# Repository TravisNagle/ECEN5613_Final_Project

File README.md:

# (WIP) Modular MIDI Control Surface for Reaper

**ECEN 5613 Embedded System Design · Fall 2026 Final Project**
Travis Nagle & Nathan Cohen

An 8051-based MIDI control surface for Reaper. Two motorized faders stay in sync with the DAW, a 16x4 LCD and panel buttons edit presets, and plug-in I2C daughter boards add pots and buttons.

> **Status (2026-10-24):** design phase, nothing built yet. The master board is the **existing class dev board**, and every new circuit is **hand-built on perf boards** (no custom PCB). The authoritative hardware spec is [Hardware_Map.md](Hardware_Map.md) **Rev 13**; open decisions are in its section 9. The PDR (10/19) described a foot controller with one fader. The changes since then are in Hardware_Map Appendix B.

## Documents

| File | What it is |
|---|---|
| [Hardware_Map.md](Hardware_Map.md) | **Authoritative hardware spec (Rev 13)**: architecture, class-board changes, pin map, memory map, netlist (Appendix A), build stages, open items |
| [hardware/kicad/ESD_Final/ESD_Final_schematic.pdf](hardware/kicad/ESD_Final/ESD_Final_schematic.pdf) | **Schematic** (KiCad 10, one sheet per board), generated from [hardware/kicad/tools/design.py](hardware/kicad/tools/design.py) |
| [hardware/panel/](hardware/panel/) | Laser-cut acrylic top panel (SVG generator) |
| [hardware/Perfboard_Order_Notes.md](hardware/Perfboard_Order_Notes.md) | Kit parts mapping, on-hand modules, Digi-Key order (not yet placed) and alternates |
| [docs/f26finalproject_8-24-2026.pdf](docs/f26finalproject_8-24-2026.pdf) | Course final-project specification (deliverables, report and submission rules) |
| [docs/F26_PDR_TravisNagle_NathanCohen.pptx](docs/F26_PDR_TravisNagle_NathanCohen.pptx) | Preliminary design review slides (10/19) |
| [docs/MIDI-Controller.pdf](docs/MIDI-Controller.pdf) | PDR-era design document (single fader) |
| [docs/archive/](docs/archive/) | Superseded documents (Rev 10 review of the dropped PCB design) |
| [reference/](reference/) | Read-only: class dev board KiCad project, BOM, Lab 3 SPLD and memory map; fader datasheet; parts-kit list |
| [AGENTS.md](AGENTS.md) | Rules and conventions for AI agents working in this repo |

The custom-PCB draft (`kicad/ESD_Main`, Rev 12) was removed on 2026-10-24. It is still in the git history at commit `735803c`.

---

## Features

- **Two motorized faders, synced both ways:** moving a fader changes Reaper's track volume, and Reaper's automation moves the fader. A capacitive touch sensor on each fader knob tells the firmware when a hand is on it, so the motor never fights the user.
- **USB-MIDI with no drivers:** the 8051 UART talks to a KB2040 acting as a class-compliant USB-MIDI device; Reaper uses its built-in Mackie Control Universal support.
- **LCD and panel buttons:** 16x4 character LCD on the memory-mapped bus, a five-way D-pad and one button per fader for menus and presets.
- **Presets:** stored in a 24C16 I2C EEPROM.
- **Expression pedal:** TRS input on the fader ADC, sent as a MIDI CC.
- **Daughter boards:** pot and button boards on an I2C bus over RJ45 cables, in any order; the master finds them by address scan.

---

## System Overview

```
                 +---------------- class dev board (master) ----------------+
 9 V adapter --> | AT89C51RC2 @ 11.0592 MHz, '373 latch, ATF16V8B decode,   |
                 | MAX232 + DB9 (FLIP / PC), 7805                           |
                 +---+-----------------+----------------+-------------+-----+
                     | AD bus + decode | PCA PWM, SPI   | UART        | I2C
                     v                 v                v             v
              LCD 16x4,          TB6612 -> 2 faders  KB2040 USB-MIDI  24C16 presets,
              '273 dir latch,    MCP3008 ADC         (level shifter)  RJ45 bus -> pot / button
              '244 buttons       (faders, pedal)         |                daughter boards
                                                         v
                                                PC: Reaper (Mackie Control)
```

Full block diagram, pin map and memory map: [Hardware_Map.md](Hardware_Map.md) sections 1-3.

| XRAM address | Device |
|---|---|
| 0x0000-0x03FF | On-chip XRAM |
| 0xF000 | Motor direction latch (write) |
| 0xF400-0xF403 | LCD (command / data / busy / data read) |
| 0xF800 | Button buffer (read) |
| 0xFFFF | Virtual debug port (logic-analyzer trigger) |

---

## Firmware Architecture

Interrupts only move bytes and set flags; all real work runs in a cooperative main loop.

| Interrupt / hardware | Job |
|---|---|
| UART (Timer 2) | Link to the KB2040: RX into a ring buffer, TX from a ring buffer. 31,250 baud MIDI or 115,200 baud packets (Hardware_Map `OPEN` #4) |
| Timer 0, mode 2 (high priority) | Soft-UART debug TX at 9,600 baud on P1.0 |
| Timer 1, mode 1 | 1 ms system tick |
| PCA | 8-bit hardware PWM at 10.8 kHz for two motors (no CPU cost) |

| Main-loop module | Job |
|---|---|
| MIDI parser | Status/data state machine, running status, real-time bytes (Reaper feedback only) |
| Button scan | Read 0xF800 at about 100 Hz, 20 ms debounce, short and long press |
| Fader control | MCP3008 reads, PD loop at 250-500 Hz, deadband brake, stall timeout, staggered starts |
| MCU link | 14-bit pitch bend both ways; touch notes from the knob touch sensors (0xF800 bit 7, P1.5) |
| Pedal | Averaging, calibration, hysteresis -> CC 11 |
| LCD + UI | Shadow copy, menu, transient messages |
| Presets | 24C16 records with checksum |
| I2C daughters | Address scan, PCF8574 buttons/LEDs, pot ADC reads, bus recovery |

The PDR's CPU budget (single fader, 1 kHz loop, MIDI merge) no longer applies. Re-measure the budget on hardware.

---

## Mackie Control Messages Used

| Message | Meaning |
|---|---|
| `E0 ll mm` / `E1 ll mm` | Fader 1 / 2 position (14-bit, both directions) |
| `90 68 7F` / `90 68 00` | Fader 1 touch / release (fader 2: note `69`) |
| `90 18+n`, `10+n`, `08+n`, `00+n` | Select / Mute / Solo / Rec for strip n |
| `90 5F 7F` / `90 5E 7F` / `90 5D 7F` | Record / Play / Stop |
| `B0 0B vv` | Expression pedal (CC 11) |

Starting point only; the full mapping is in Hardware_Map section 5.

---

## Setup

### Hardware
1. Power everything from one **9 V, 2 A or more** adapter in the class board jack; it feeds the logic and the fader motors (Hardware_Map section 3.9).
2. Plug the KB2040 into the PC by USB-C. It shows up as a USB-MIDI device.
3. Set `JP_RX` to **KB** for normal use, or **PC** for FLIP and the DB9 terminal.

### Reaper
1. **Options → Preferences → Audio → MIDI Devices:** confirm the KB2040 appears; enable its input and output.
2. **Preferences → Control/OSC/Web → Add → Mackie Control Universal:** set the MIDI input and output to the KB2040.
3. Optional: assign the pedal to any plugin parameter with **Param → Learn** in the FX window.

### Fallback (if the USB-MIDI bridge fails)
MIDI bytes go out the class board DB9 at 115,200 baud → USB-RS232 adapter → [Hairless MIDI](https://projectgus.github.io/hairless-midiserial/) → [loopMIDI](https://www.tobias-erichsen.de/software/loopmidi.html) → Reaper.

---

## Building and Flashing

> Firmware is not written yet; these steps will be finalized with the first build.

```bash
cd firmware
sdcc -mmcs51 --model-large main.c
packihx main.ihx > main.hex
```

Flash `main.hex` with Atmel FLIP over the class board DB9 (`JP_RX` in the **PC** position; hold the PSEN button through reset to enter the bootloader). The KB2040 runs a CircuitPython bridge script (to be added under `firmware/`).

---

## Milestones

Rebased from the PDR milestones for the Rev 13 scope; the team still needs to confirm owners and dates.

| | Milestone | Owner | Target | Phase |
|---|---|---|---|---|
| M1 | MIDI link: Timer 2 UART, KB2040 bridge, Reaper receives notes | Both | 11/1 | P1 |
| M2 | Debug port, panel buttons via the '244 | Travis | 11/8 | P1 |
| M3 | MCP3008: fader positions and pedal as CC | Nathan | 11/8 | P1 |
| M4 | MIDI from Reaper: parser, MCU feedback | Travis | 11/22 | P1 |
| M5 | LCD, presets (24C16), menu | Travis | 11/29 | P1-P2 |
| M6 | Motorized faders: TB6612, PD loop, MCU link (2 faders) | Nathan | 11/29 | P1-P2 |
| M7 | I2C daughter boards (pot, button) over RJ45 | Both | 11/29 | P3 |
| M8 | Stretch: MIDI clock tempo sync | Both | If ahead | |

Feature freeze **11/30** · Demo **12/4** · Return kit items (including the NVSRAM) **12/7** · Report **12/9**

---

## Repository Layout

```
Hardware_Map.md   hardware spec (start here)
hardware/         kicad/ (schematic project, libraries, generators), panel/ (acrylic panel), parts and order notes
spld/             (planned) final.pld, its simulation input and .jed
firmware/         8051 C source (SDCC) and the KB2040 bridge script
tools/            test scripts (MIDI-OX configs, benchmarks)
docs/             course spec, PDR deck, design doc; archive/ for superseded documents
reference/        class dev board, fader datasheet, parts kit; read-only: copy, do not edit
```

---

## References

- Atmel AT89C51RB2/RC2 Datasheet (doc4180), Errata (doc4181), 8051 Hardware Manual (doc4316)
- [MIDI 1.0 Electrical Specification (CA-033)](https://midi.org/wp-content/uploads/wpforo/default_attachments/1709416667-ca33-MIDI-10-Electrical-Specification-Update.pdf)
- [Summary of MIDI 1.0 Messages](https://midi.org/summary-of-midi-1-0-messages)
- [REAPER Mackie Control source (`csurf_mcu.cpp`)](https://github.com/justinfrankel/reaper-sdk/blob/main/reaper-plugins/reaper_csurf/csurf_mcu.cpp)
- [Microchip MCP3008](https://ww1.microchip.com/downloads/en/DeviceDoc/21295d.pdf), Toshiba TB6612FNG, TI [SN74AHC157](https://www.ti.com/lit/ds/symlink/sn74ahc157.pdf), [SN74HCT244](https://www.ti.com/lit/ds/symlink/sn74hct244.pdf), [CD74HCT273](https://www.ti.com/lit/ds/symlink/cd74hct273.pdf), [MAX232](https://www.ti.com/lit/ds/symlink/max232.pdf), NXP PCF8574
- [Adafruit KB2040](https://learn.adafruit.com/adafruit-kb2040), CircuitPython `usb_midi`
- Terwin SM100 motor fader: [reference/motor_slider_datasheet.pdf](reference/motor_slider_datasheet.pdf)

## AI use

Parts of the hardware documents were drafted with AI assistance (Anthropic Claude) and reviewed by the team. The course requires AI use to be fully documented in the final report, and AI may not be used to write report text.

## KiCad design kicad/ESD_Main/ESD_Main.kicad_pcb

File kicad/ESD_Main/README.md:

# ESD_Main: main board (KiCad 10)

**Status (2026-10-20, 02:10): first complete draft, DO NOT ORDER YET.** Schematic: ERC 0 violations, netlist matches the design data (178 parts, 555 pins). PCB: 100 % routed by Freerouting, DRC 0 errors / 0 unconnected / 0 schematic-parity issues; the only warnings are 14 `silk_edge_clearance` on the edge connectors (silk at the board edge by design). It has not been reviewed by a person in KiCad yet; work through the checklist below first.

Spec: [Hardware_Map.md](../../Hardware_Map.md) Rev 12 (pin map section 3.2, netlist Appendix A, open items section 9). Schematic PDF: [ESD_Main_schematic.pdf](ESD_Main_schematic.pdf). Renders: [top](fab/ESD_Main_top.png), [bottom](fab/ESD_Main_bottom.png). Fab files: [fab/](fab/) (Gerbers + drill zip for JLCPCB, BOM CSV).

## What is on the board

- 200 x 150 mm, 2 layers, 1.6 mm, GND pour both sides. The PCB is the **front panel**: faders, LCD, D-pad and buttons on top.
- **Three Terwin SM100 motor faders** (footprint from [the datasheet](../../reference/motor_slider_datasheet.pdf)) along the 150 mm depth; each motor hangs through a **26 x 3.2 mm notch** in the back edge. Motor wires go to 2-pin headers MOTOR 1-3 (J10-J12). H-bridges U12/U13 sit between the faders; fader buttons SW8-SW10 beside each fader's front end (no room below them).
- **LCD** (Lab 4 kit: Samsung 16x4, 14-pin single row, no backlight) on 15 mm+ M2.5 standoffs and a tall header **over the bus logic** (8051, '373, SPLD, '273, '244, '14, EEPROM). The LCD lifts off for debugging; the test points are outside its outline.
- Back edge: 12 V barrel (J1), MIDI IN/OUT DIN-5 (J5/J6), pedal TRS (J13). Left edge: PC DB9 (J7). Front: D-pad, RESET, BOOT (PSEN), contrast trimmer, power/status LEDs, TTL PC (J8) and TTL DEBUG (J9) FTDI-style headers, daughter-bus IDC (J14), test points.
- Reference designators differ from the spec's (for example spec U7 SPLD = board U4, spec J10 LCD = board J4); each part's `Note` field in the schematic gives the spec name.

## Check before ordering (needs a person)

1. **Fader footprint**: print the top copper/silk at 1:1 (or use KiCad's 3D/measure) and lay a real fader on it: pins 1/2 and 3/T, the two locating bosses (Ø2.1 NPTH at ±48 mm) and the motor notch.
2. **LCD**: confirm with a ruler: outline 87 x 60, holes 82 x 55 apart, pin 1 at 10.0 mm from the left edge and 2.5 mm from the top. Count 16 vs 20 characters at first power-up (firmware constant).
3. **DIN-5 (Same Sky SDS-50J)** and **barrel jack** orientation: mating faces flush with the back edge (check the 3D view).
4. **Standoffs**: board standoffs >= 16 mm (motor + terminals stick out about 14.5 mm below the top surface); LCD standoffs high enough to clear the socketed DIPs underneath.
5. Run DRC in KiCad, view all copper layers, and look at the motor/12 V traces (1.0/1.2 mm) and the long ADC SPI traces that run under the faders.
6. JLCPCB: upload `fab/ESD_Main_gerbers.zip`; 2 layers, 1.6 mm, HASL lead-free, order a stencil for the 0805 parts.
7. BOM: `fab/ESD_Main_BOM.csv` has MPNs; supplier, URL and cost columns are still blank (course BOM needs them).

## How it was made (and how to change it)

The schematic and the initial board were **generated by scripts** from two data files, then auto-routed with Freerouting 1.9.0:

| File | Role |
|---|---|
| [kicad/tools/esd_main_design.py](../tools/esd_main_design.py) | every part: symbol, footprint, phase, MPN, pin -> net |
| [kicad/tools/esd_main_placement.py](../tools/esd_main_placement.py) | board outline, notches, fixed positions, placement zones |
| [kicad/tools/gen_esd_main.py](../tools/gen_esd_main.py) | writes the schematic (ERC + netlist checked) |
| [kicad/tools/gen_esd_main_pcb.py](../tools/gen_esd_main_pcb.py) | builds, routes (Freerouting) and exports the board |
| [kicad/tools/check_esd_main.py](../tools/check_esd_main.py) | netlist export vs design data cross-check |

```bash
python3 kicad/tools/gen_esd_main.py
KPY=/Applications/KiCad/KiCad.app/Contents/Frameworks/Python.framework/Versions/Current/bin/python3
$KPY kicad/tools/gen_esd_main_pcb.py --stage all --jar /path/to/freerouting-1.9.0.jar --work /tmp/esd_route
```

`--jar` and `--work` default to a path on Nathan's machine, so pass your own. Freerouting needs Java 17+ and is random: each run takes 2-5 minutes and results vary.

**Important**: regenerating overwrites the schematic and board. Once anyone hand-edits in KiCad (routing clean-up, moving parts), stop regenerating the board and make further changes in KiCad (keep the design data file in step for the schematic, or edit the schematic in KiCad too and say so here).

AI use: the schematic/PCB generators and this draft were produced with AI assistance (Anthropic Claude) and must be reviewed by the team; record this in the final report.

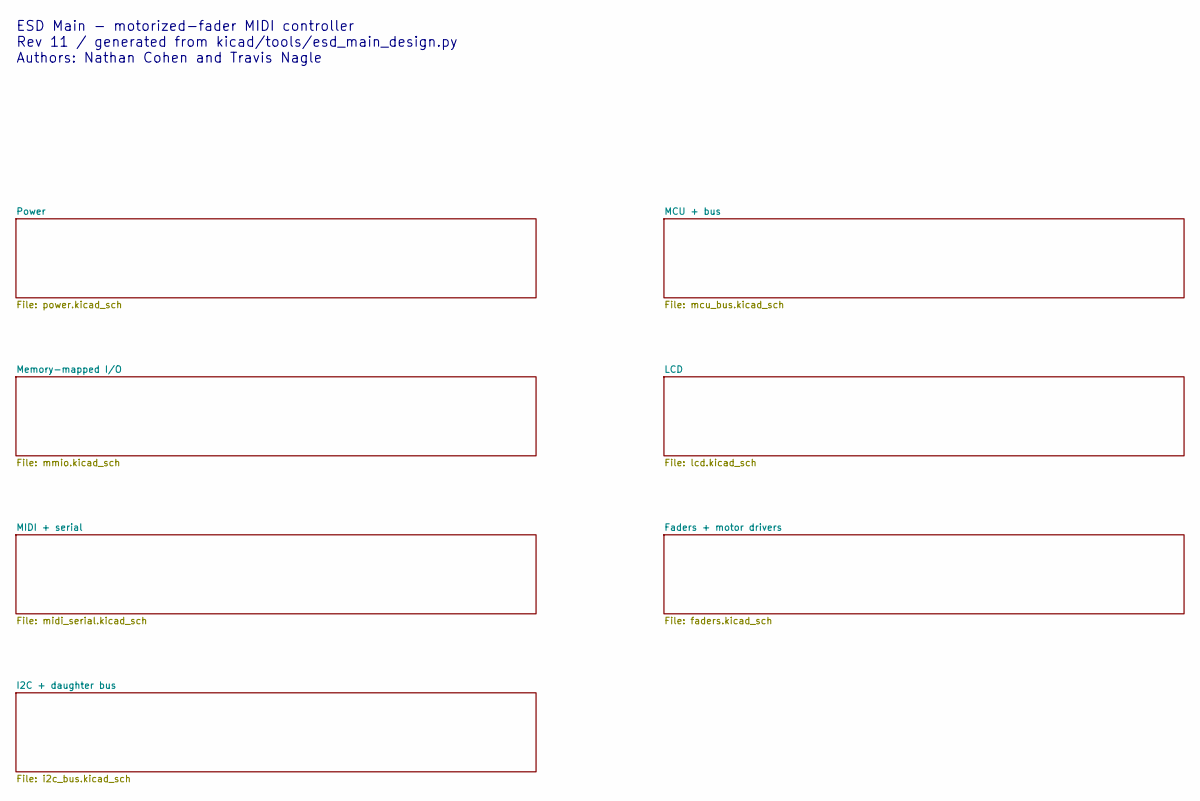
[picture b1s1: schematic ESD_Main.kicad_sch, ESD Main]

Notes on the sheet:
ESD Main - motorized-fader MIDI controller Rev 11 / generated from kicad/tools/esd_main_design.py Authors: Nathan Cohen and Travis Nagle

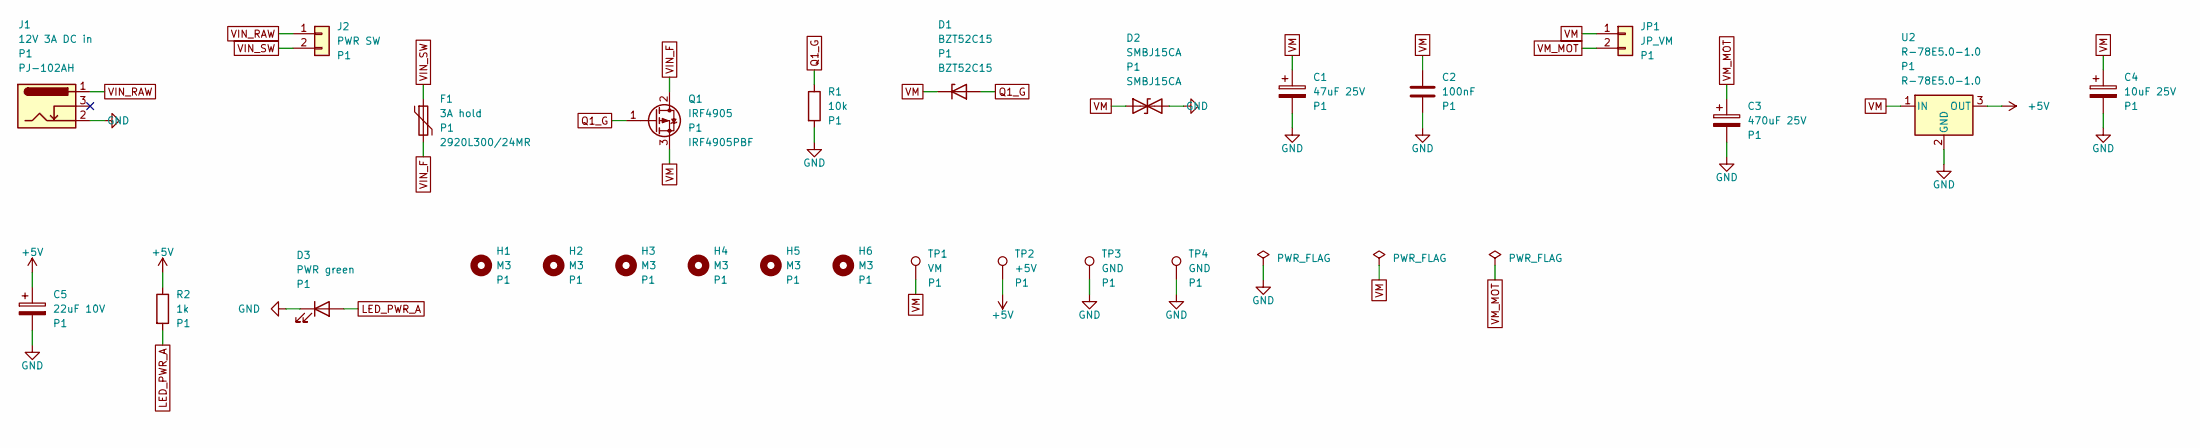
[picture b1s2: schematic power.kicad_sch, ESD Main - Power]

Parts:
C1: 47uF 25V; CP_Radial_D6.3mm_P2.50mm
C2: 100nF; C_0805_2012Metric
C3: 470uF 25V; CP_Radial_D10.0mm_P5.00mm
C4: 10uF 25V; CP_Radial_D5.0mm_P2.00mm
C5: 22uF 10V; CP_Radial_D5.0mm_P2.00mm
D1: BZT52C15; D_SOD-123; MPN BZT52C15
D2: SMBJ15CA; D_SMB; MPN SMBJ15CA
D3: PWR green; LED_0805_2012Metric
F1: 3A hold; Fuse_2920_7451Metric; MPN 2920L300/24MR
H1, H2, H3, H4, H5, H6: M3; MountingHole_3.2mm_M3
J1: 12V 3A DC in; BarrelJack_CUI_PJ-102AH_Horizontal; MPN PJ-102AH
J2: PWR SW; PinHeader_1x02_P2.54mm_Vertical
JP1: JP_VM; PinHeader_1x02_P2.54mm_Vertical
Q1: IRF4905; TO-220-3_Vertical; MPN IRF4905PBF
R1: 10k; R_0805_2012Metric
R2: 1k; R_0805_2012Metric
TP1: VM; TestPoint_THTPad_D1.5mm_Drill0.7mm
TP2: +5V; TestPoint_THTPad_D1.5mm_Drill0.7mm
TP3, TP4: GND; TestPoint_THTPad_D1.5mm_Drill0.7mm
U2: R-78E5.0-1.0; TO-220-3_Vertical; MPN R-78E5.0-1.0

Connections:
+5V: C5.1, R2.1, TP2.1, U2.3 (OUT); also elsewhere on the board
GND: C1.2, C2.2, C3.2, C4.2, C5.2, D2.2 (A2), D3.1 (K), J1.2, R1.2, TP3.1, TP4.1, U2.2 (GND); also elsewhere on the board
LED_PWR_A: D3.2 (A), R2.2
Q1_G: D1.2 (A), Q1.1 (G), R1.1
VIN_F: F1.2, Q1.2 (D)
VIN_RAW: J1.1, J2.1
VIN_SW: F1.1, J2.2
VM: C1.1, C2.1, C4.1, D1.1 (K), D2.1 (A1), JP1.1, Q1.3 (S), TP1.1, U2.1 (IN)
VM_MOT: C3.1, JP1.2; also elsewhere on the board

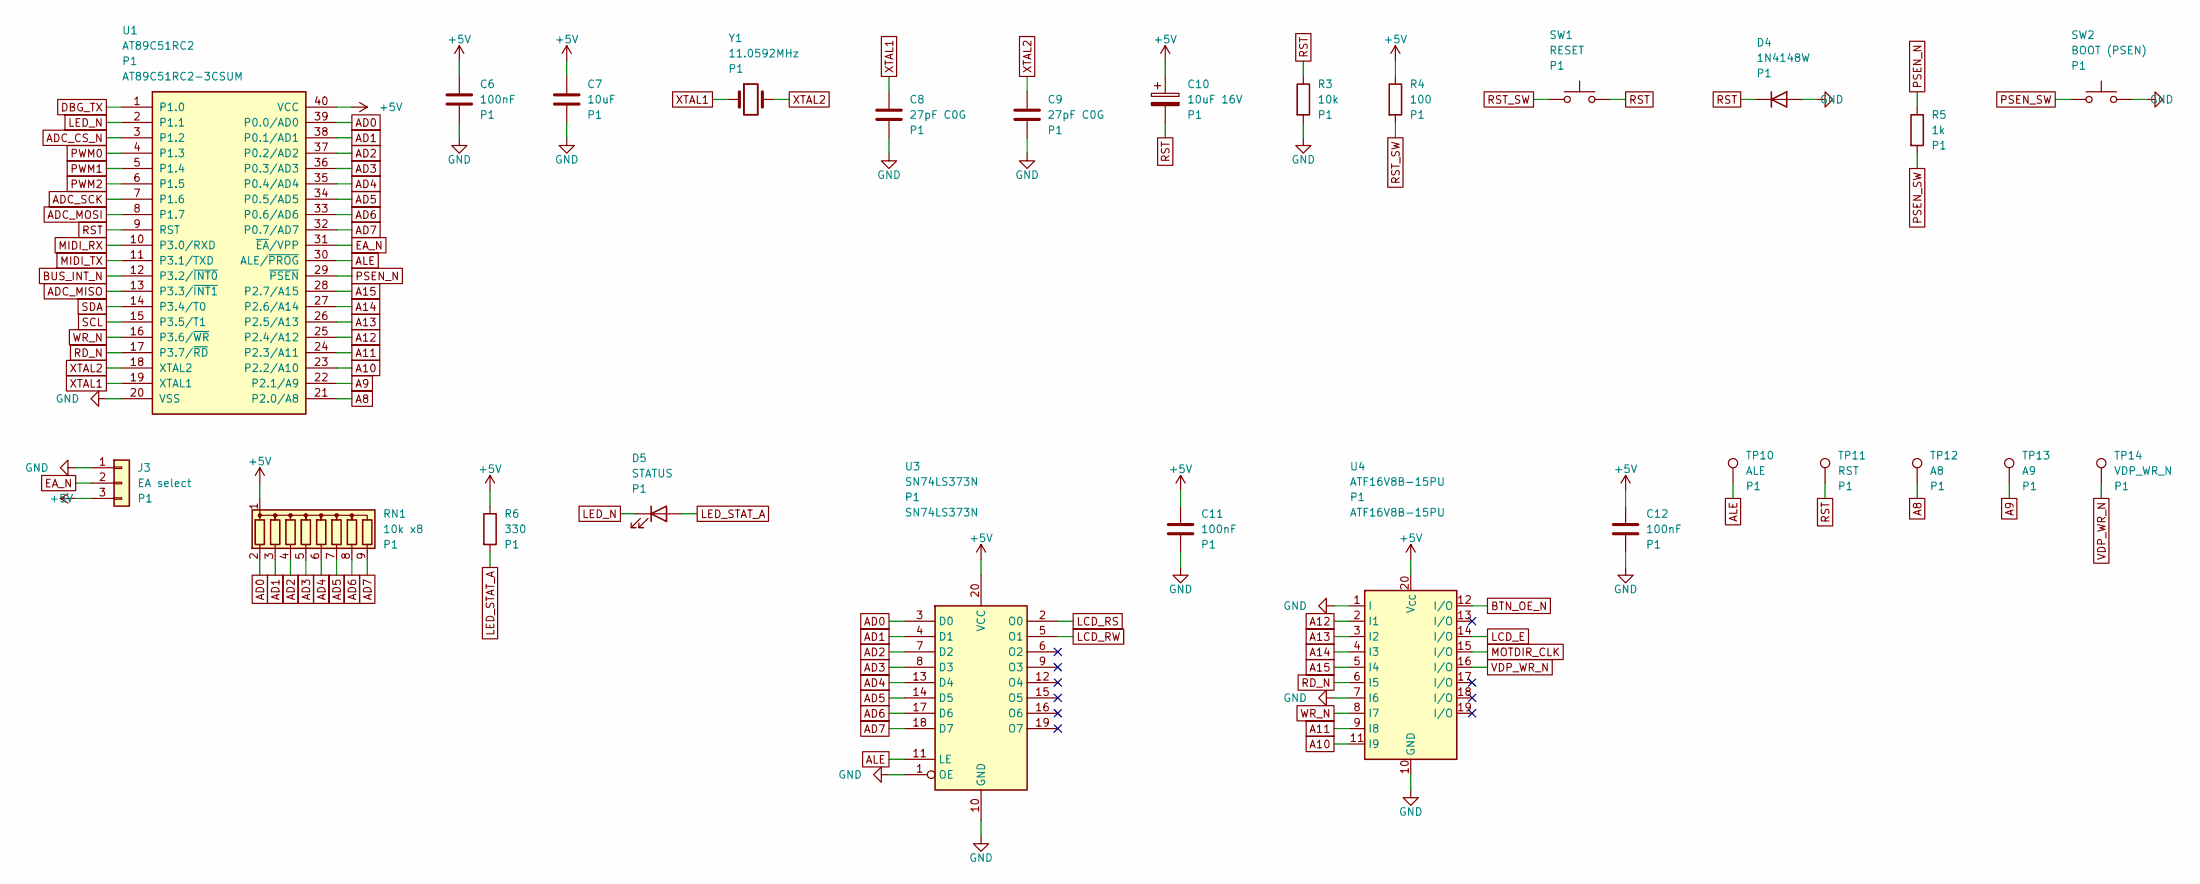
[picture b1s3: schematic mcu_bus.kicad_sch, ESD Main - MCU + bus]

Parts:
C6, C11, C12: 100nF; C_0805_2012Metric
C7: 10uF; C_0805_2012Metric
C8, C9: 27pF C0G; C_0805_2012Metric
C10: 10uF 16V; CP_Radial_D5.0mm_P2.00mm
D4: 1N4148W; D_SOD-123
D5: STATUS; LED_0805_2012Metric
J3: EA select; PinHeader_1x03_P2.54mm_Vertical
R3: 10k; R_0805_2012Metric
R4: 100; R_0805_2012Metric
R5: 1k; R_0805_2012Metric
R6: 330; R_0805_2012Metric
RN1: 10k x8; R_Array_SIP9
SW1: RESET; SW_PUSH_6mm
SW2: BOOT (PSEN); SW_PUSH_6mm
TP10: ALE; TestPoint_THTPad_D1.5mm_Drill0.7mm
TP11: RST; TestPoint_THTPad_D1.5mm_Drill0.7mm
TP12: A8; TestPoint_THTPad_D1.5mm_Drill0.7mm
TP13: A9; TestPoint_THTPad_D1.5mm_Drill0.7mm
TP14: VDP_WR_N; TestPoint_THTPad_D1.5mm_Drill0.7mm
U1: AT89C51RC2; DIP-40_W15.24mm_Socket; MPN AT89C51RC2-3CSUM
U3: SN74LS373N; DIP-20_W7.62mm_Socket; MPN SN74LS373N
U4: ATF16V8B-15PU; DIP-20_W7.62mm_Socket; MPN ATF16V8B-15PU
Y1: 11.0592MHz; Crystal_HC49-U_Vertical

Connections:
+5V: C6.1, C7.1, C10.1, C11.1, C12.1, J3.3, R4.1, R6.1, RN1.1 (common), U1.40 (VCC), U3.20 (VCC), U4.20 (V_{CC}); also elsewhere on the board
A8: TP12.1, U1.21 (P2.0/A8)
A9: TP13.1, U1.22 (P2.1/A9)
A10: U1.23 (P2.2/A10), U4.11 (I9)
A11: U1.24 (P2.3/A11), U4.9 (I8)
A12: U1.25 (P2.4/A12), U4.2 (I1)
A13: U1.26 (P2.5/A13), U4.3 (I2)
A14: U1.27 (P2.6/A14), U4.4 (I3)
A15: U1.28 (P2.7/A15), U4.5 (I4)
AD0: RN1.2 (R1), U1.39 (P0.0/AD0), U3.3 (D0); also elsewhere on the board
AD1: RN1.3 (R2), U1.38 (P0.1/AD1), U3.4 (D1); also elsewhere on the board
AD2: RN1.4 (R3), U1.37 (P0.2/AD2), U3.7 (D2); also elsewhere on the board
AD3: RN1.5 (R4), U1.36 (P0.3/AD3), U3.8 (D3); also elsewhere on the board
AD4: RN1.6 (R5), U1.35 (P0.4/AD4), U3.13 (D4); also elsewhere on the board
AD5: RN1.7 (R6), U1.34 (P0.5/AD5), U3.14 (D5); also elsewhere on the board
AD6: RN1.8 (R7), U1.33 (P0.6/AD6), U3.17 (D6); also elsewhere on the board
AD7: RN1.9 (R8), U1.32 (P0.7/AD7), U3.18 (D7); also elsewhere on the board
ADC_CS_N: U1.3 (P1.2); also elsewhere on the board
ADC_MISO: U1.13 (P3.3/~INT1); also elsewhere on the board
ADC_MOSI: U1.8 (P1.7); also elsewhere on the board
ADC_SCK: U1.7 (P1.6); also elsewhere on the board
ALE: TP10.1, U1.30 (ALE/~PROG), U3.11 (LE)
BTN_OE_N: U4.12 (I/O); also elsewhere on the board
BUS_INT_N: U1.12 (P3.2/~INT0); also elsewhere on the board
DBG_TX: U1.1 (P1.0); also elsewhere on the board
EA_N: J3.2, U1.31 (~EA/VPP)
GND: C6.2, C7.2, C8.2, C9.2, C11.2, C12.2, D4.2 (A), J3.1, R3.2, SW2.2, U1.20 (VSS), U3.1 (OE), U3.10 (GND), U4.1 (I), U4.7 (I6), U4.10 (GND); also elsewhere on the board
LCD_E: U4.14 (I/O); also elsewhere on the board
LCD_RS: U3.2 (O0); also elsewhere on the board
LCD_RW: U3.5 (O1); also elsewhere on the board
LED_N: D5.1 (K), U1.2 (P1.1)
LED_STAT_A: D5.2 (A), R6.2
MIDI_RX: U1.10 (P3.0/RXD); also elsewhere on the board
MIDI_TX: U1.11 (P3.1/TXD); also elsewhere on the board
MOTDIR_CLK: U4.15 (I/O); also elsewhere on the board
PSEN_N: R5.1, U1.29 (~PSEN)
PSEN_SW: R5.2, SW2.1
PWM0: U1.4 (P1.3); also elsewhere on the board
PWM1: U1.5 (P1.4); also elsewhere on the board
PWM2: U1.6 (P1.5); also elsewhere on the board
RD_N: U1.17 (P3.7/~RD), U4.6 (I5)
RST: C10.2, D4.1 (K), R3.1, SW1.2, TP11.1, U1.9 (RST); also elsewhere on the board
RST_SW: R4.2, SW1.1
SCL: U1.15 (P3.5/T1); also elsewhere on the board
SDA: U1.14 (P3.4/T0); also elsewhere on the board
VDP_WR_N: TP14.1, U4.16 (I/O)
WR_N: U1.16 (P3.6/~WR), U4.8 (I7)
XTAL1: C8.1, U1.19 (XTAL1), Y1.1
XTAL2: C9.1, U1.18 (XTAL2), Y1.2

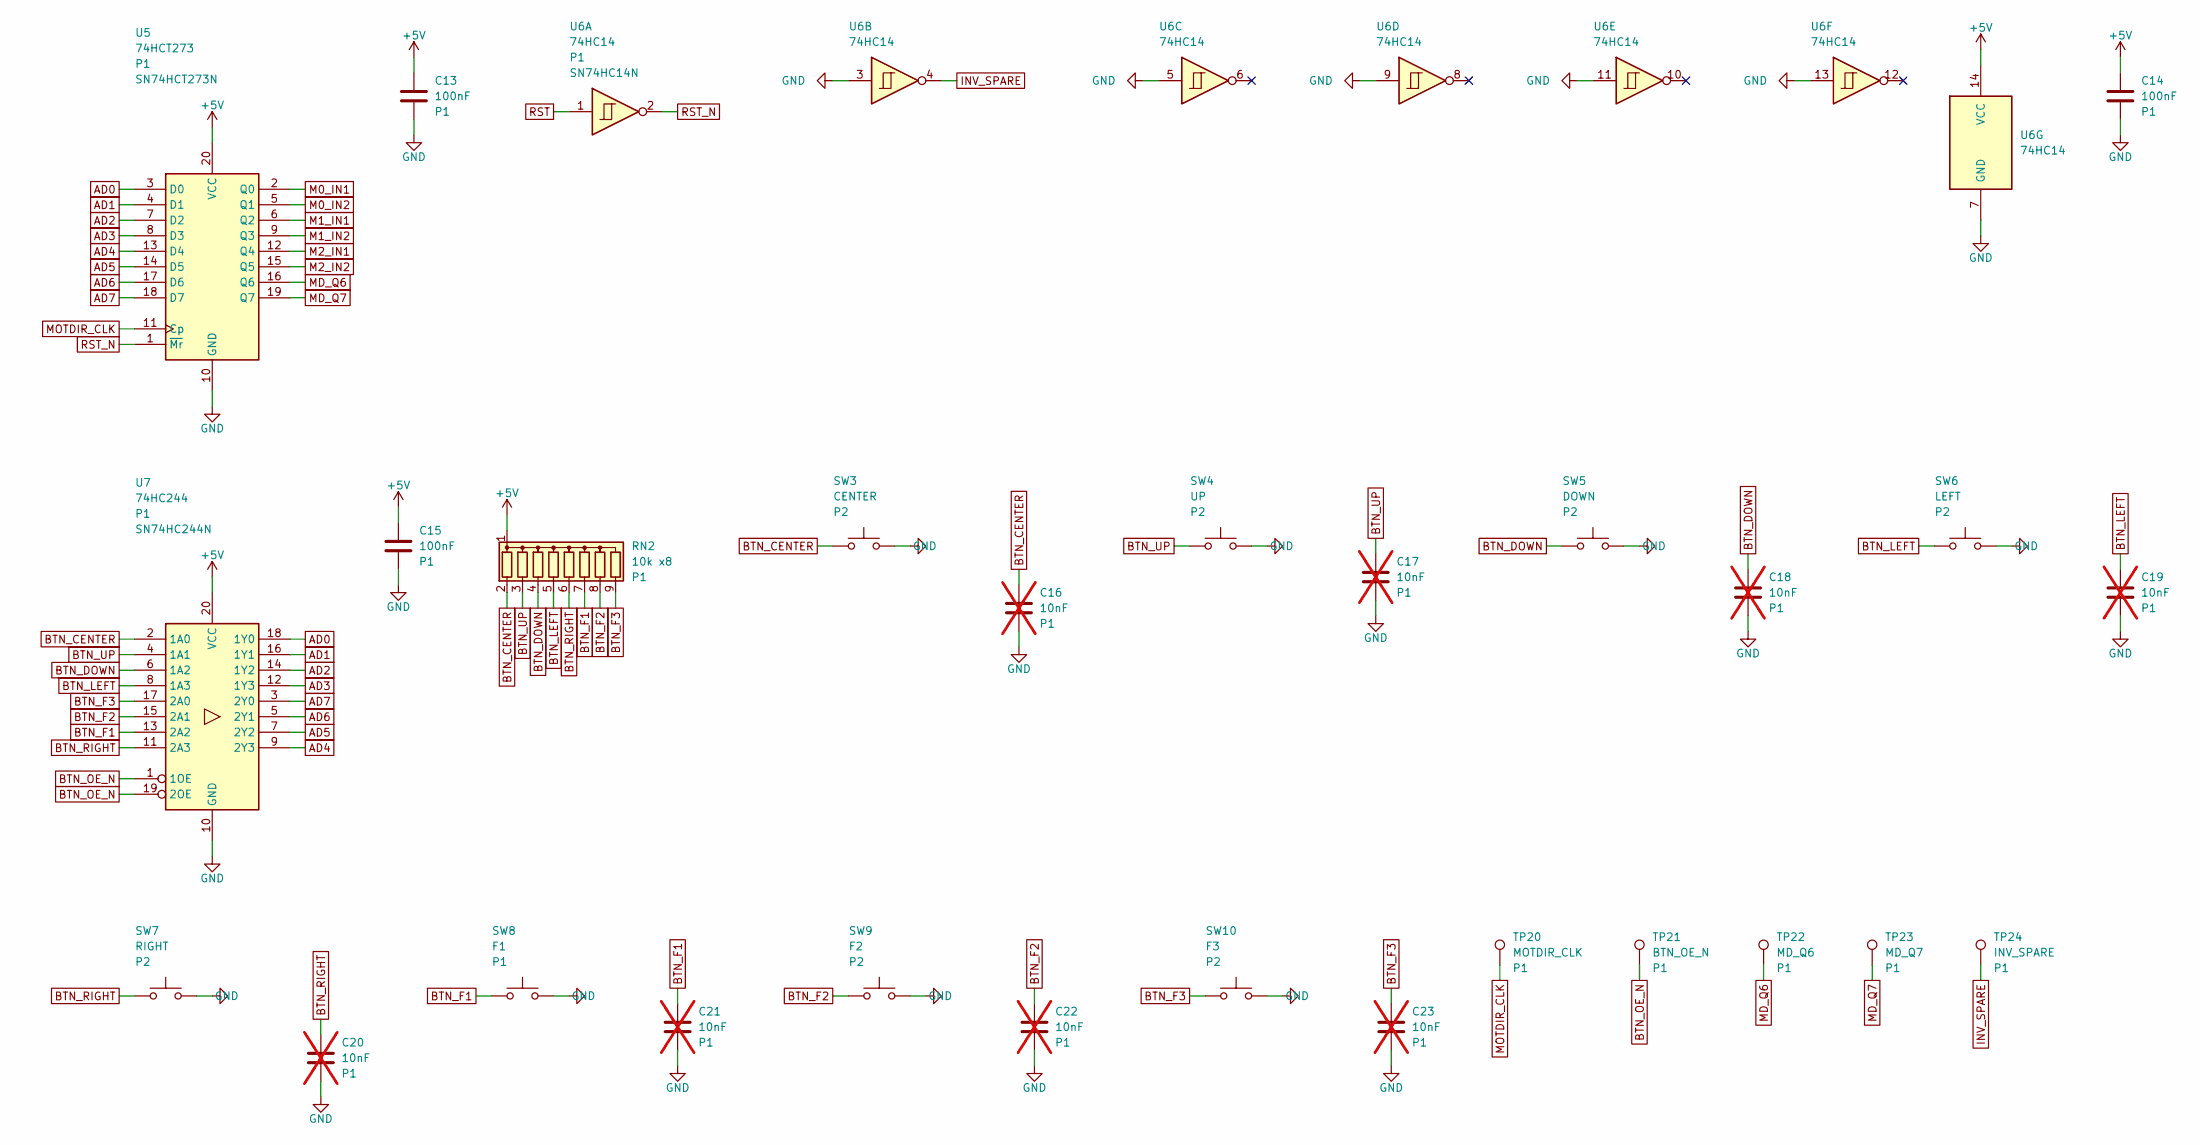
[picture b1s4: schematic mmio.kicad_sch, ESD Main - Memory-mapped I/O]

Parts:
C13, C14, C15: 100nF; C_0805_2012Metric
C16, C17, C18, C19, C20, C21, C22, C23: 10nF; C_0805_2012Metric; not fitted
RN2: 10k x8; R_Array_SIP9
SW3: CENTER; SW_PUSH_6mm
SW4: UP; SW_PUSH_6mm
SW5: DOWN; SW_PUSH_6mm
SW6: LEFT; SW_PUSH_6mm
SW7: RIGHT; SW_PUSH_6mm
SW8: F1; SW_PUSH_6mm
SW9: F2; SW_PUSH_6mm
SW10: F3; SW_PUSH_6mm
TP20: MOTDIR_CLK; TestPoint_THTPad_D1.5mm_Drill0.7mm
TP21: BTN_OE_N; TestPoint_THTPad_D1.5mm_Drill0.7mm
TP22: MD_Q6; TestPoint_THTPad_D1.5mm_Drill0.7mm
TP23: MD_Q7; TestPoint_THTPad_D1.5mm_Drill0.7mm
TP24: INV_SPARE; TestPoint_THTPad_D1.5mm_Drill0.7mm
U5: 74HCT273; DIP-20_W7.62mm_Socket; MPN SN74HCT273N
U6: 74HC14; DIP-14_W7.62mm_Socket; MPN SN74HC14N
U7: 74HC244; DIP-20_W7.62mm_Socket; MPN SN74HC244N

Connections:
+5V: C13.1, C14.1, C15.1, RN2.1 (common), U5.20 (VCC), U6.14 (VCC), U7.20 (VCC); also elsewhere on the board
AD0: U5.3 (D0), U7.18 (1Y0); also elsewhere on the board
AD1: U5.4 (D1), U7.16 (1Y1); also elsewhere on the board
AD2: U5.7 (D2), U7.14 (1Y2); also elsewhere on the board
AD3: U5.8 (D3), U7.12 (1Y3); also elsewhere on the board
AD4: U5.13 (D4), U7.9 (2Y3); also elsewhere on the board
AD5: U5.14 (D5), U7.7 (2Y2); also elsewhere on the board
AD6: U5.17 (D6), U7.5 (2Y1); also elsewhere on the board
AD7: U5.18 (D7), U7.3 (2Y0); also elsewhere on the board
BTN_CENTER: C16.1, RN2.2 (R1), SW3.1, U7.2 (1A0)
BTN_DOWN: C18.1, RN2.4 (R3), SW5.1, U7.6 (1A2)
BTN_F1: C21.1, RN2.7 (R6), SW8.1, U7.13 (2A2)
BTN_F2: C22.1, RN2.8 (R7), SW9.1, U7.15 (2A1)
BTN_F3: C23.1, RN2.9 (R8), SW10.1, U7.17 (2A0)
BTN_LEFT: C19.1, RN2.5 (R4), SW6.1, U7.8 (1A3)
BTN_OE_N: TP21.1, U7.1 (1OE), U7.19 (2OE); also elsewhere on the board
BTN_RIGHT: C20.1, RN2.6 (R5), SW7.1, U7.11 (2A3)
BTN_UP: C17.1, RN2.3 (R2), SW4.1, U7.4 (1A1)
GND: C13.2, C14.2, C15.2, C16.2, C17.2, C18.2, C19.2, C20.2, C21.2, C22.2, C23.2, SW3.2, SW4.2, SW5.2, SW6.2, SW7.2, SW8.2, SW9.2, SW10.2, U5.10 (GND), U6.3, U6.5, U6.7 (GND), U6.9, U6.11, U6.13, U7.10 (GND); also elsewhere on the board
INV_SPARE: TP24.1, U6.4
M0_IN1: U5.2 (Q0); also elsewhere on the board
M0_IN2: U5.5 (Q1); also elsewhere on the board
M1_IN1: U5.6 (Q2); also elsewhere on the board
M1_IN2: U5.9 (Q3); also elsewhere on the board
M2_IN1: U5.12 (Q4); also elsewhere on the board
M2_IN2: U5.15 (Q5); also elsewhere on the board
MD_Q6: TP22.1, U5.16 (Q6)
MD_Q7: TP23.1, U5.19 (Q7)
MOTDIR_CLK: TP20.1, U5.11 (Cp); also elsewhere on the board
RST: U6.1; also elsewhere on the board
RST_N: U5.1 (~Mr), U6.2

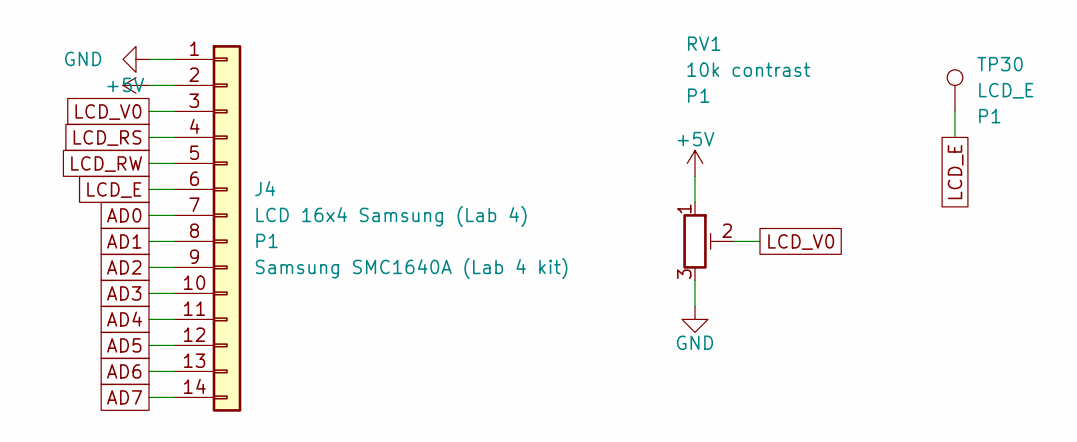
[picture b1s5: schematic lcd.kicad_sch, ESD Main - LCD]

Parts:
J4: LCD 16x4 Samsung (Lab 4); LCD_16x4_Samsung_87x60_Header1x14; MPN Samsung SMC1640A (Lab 4 kit)
RV1: 10k contrast; Potentiometer_Bourns_3296W_Vertical
TP30: LCD_E; TestPoint_THTPad_D1.5mm_Drill0.7mm

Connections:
+5V: J4.2, RV1.1; also elsewhere on the board
AD0: J4.7; also elsewhere on the board
AD1: J4.8; also elsewhere on the board
AD2: J4.9; also elsewhere on the board
AD3: J4.10; also elsewhere on the board
AD4: J4.11; also elsewhere on the board
AD5: J4.12; also elsewhere on the board
AD6: J4.13; also elsewhere on the board
AD7: J4.14; also elsewhere on the board
GND: J4.1, RV1.3; also elsewhere on the board
LCD_E: J4.6, TP30.1; also elsewhere on the board
LCD_RS: J4.4; also elsewhere on the board
LCD_RW: J4.5; also elsewhere on the board
LCD_V0: J4.3, RV1.2

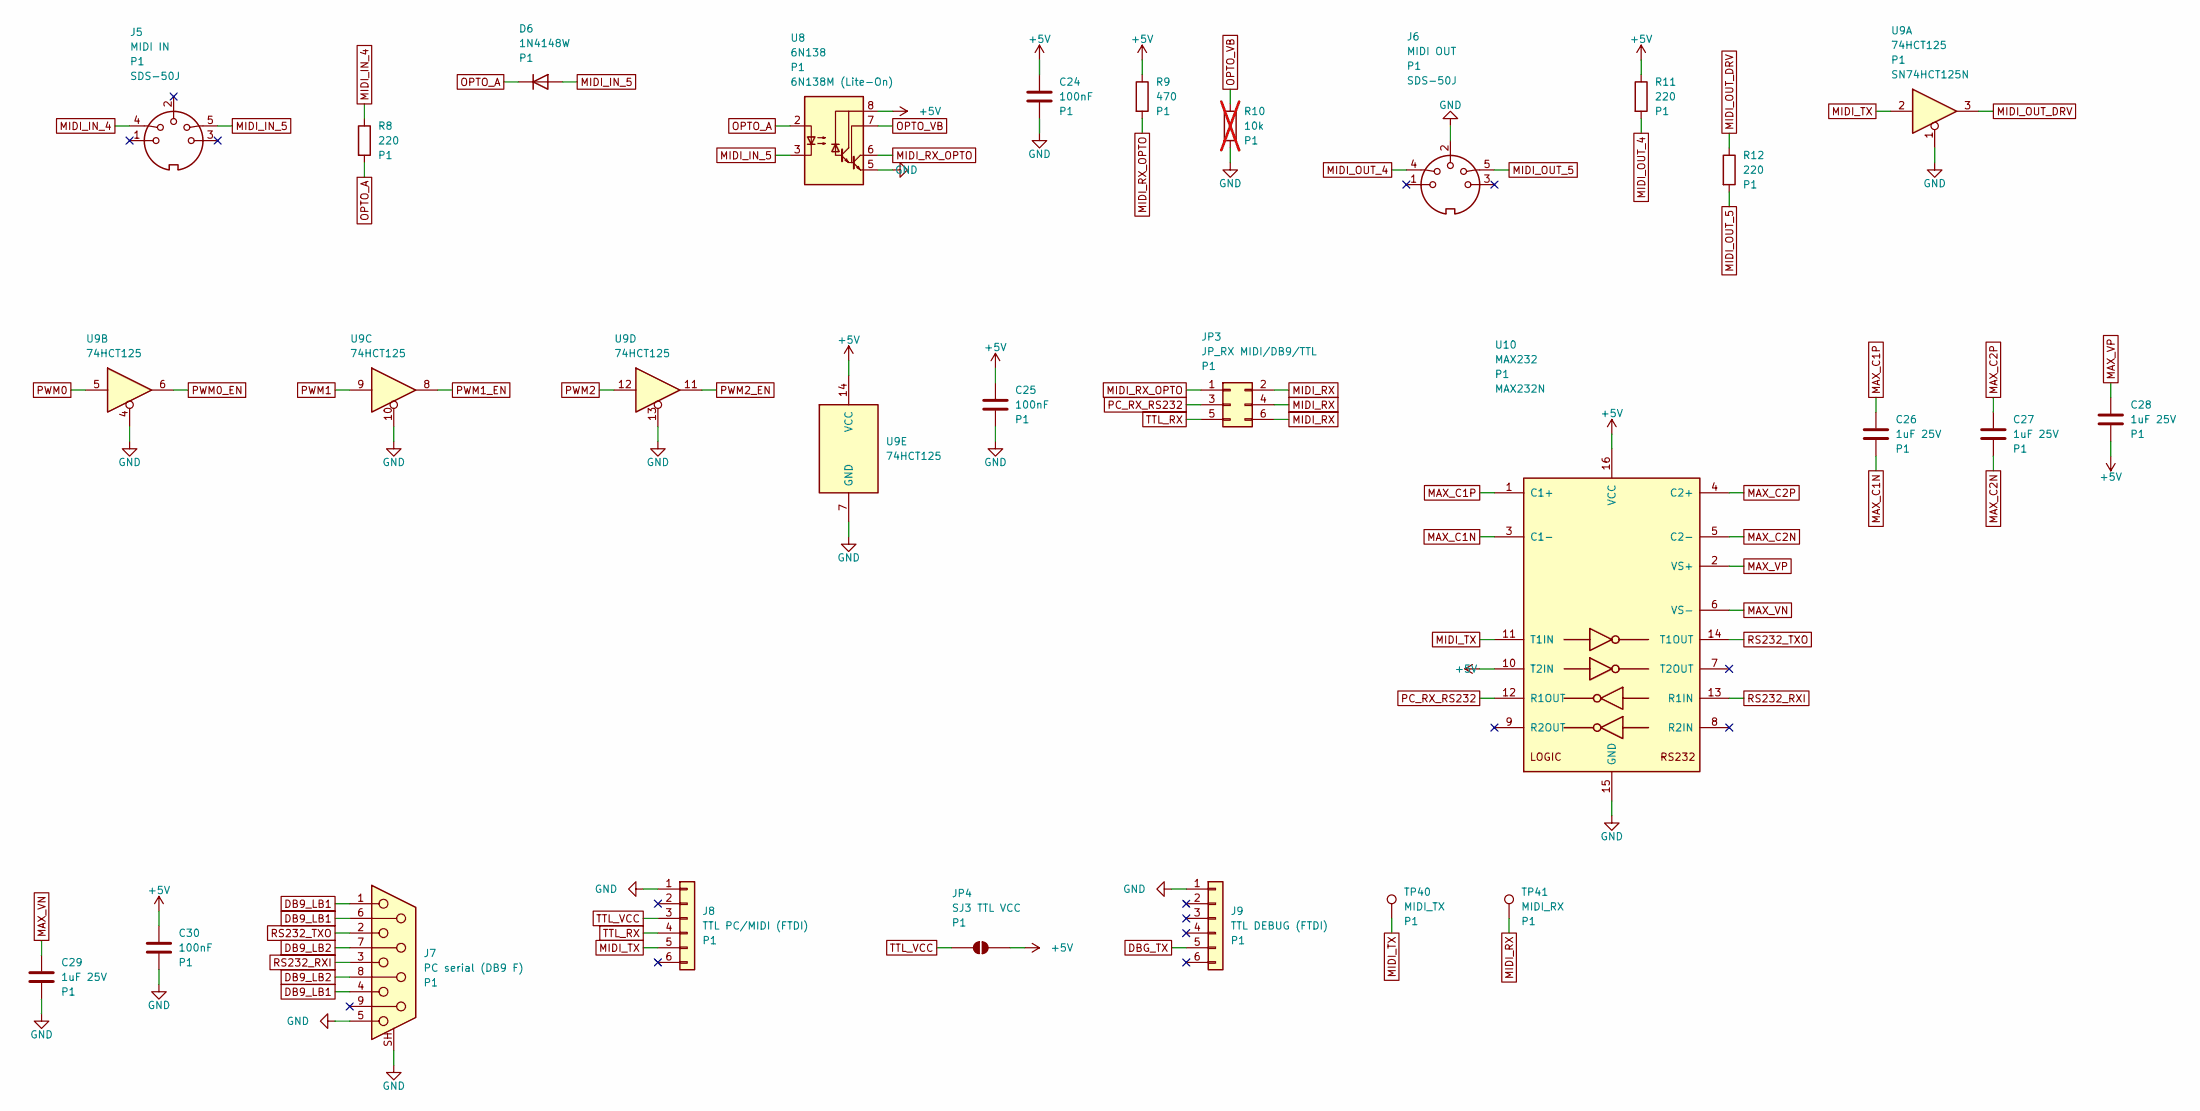
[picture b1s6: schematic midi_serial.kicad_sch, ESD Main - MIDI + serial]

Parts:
C24, C25, C30: 100nF; C_0805_2012Metric
C26, C27, C28, C29: 1uF 25V; C_0805_2012Metric
D6: 1N4148W; D_SOD-123
J5: MIDI IN; DIN-5_180deg_SameSky_SDS-50J; MPN SDS-50J
J6: MIDI OUT; DIN-5_180deg_SameSky_SDS-50J; MPN SDS-50J
J7: PC serial (DB9 F); DSUB-9_Socket_Horizontal_P2.77x2.84mm_EdgePinOffset7.70mm_H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
J8: TTL PC/MIDI (FTDI); PinHeader_1x06_P2.54mm_Vertical
J9: TTL DEBUG (FTDI); PinHeader_1x06_P2.54mm_Vertical
JP3: JP_RX MIDI/DB9/TTL; PinHeader_2x03_P2.54mm_Vertical
JP4: SJ3 TTL VCC; SolderJumper-2_P1.3mm_Open_RoundedPad1.0x1.5mm
R8, R11, R12: 220; R_0805_2012Metric
R9: 470; R_0805_2012Metric
R10: 10k; R_0805_2012Metric; not fitted
TP40: MIDI_TX; TestPoint_THTPad_D1.5mm_Drill0.7mm
TP41: MIDI_RX; TestPoint_THTPad_D1.5mm_Drill0.7mm
U8: 6N138; DIP-8_W7.62mm_Socket; MPN 6N138M (Lite-On)
U9: 74HCT125; DIP-14_W7.62mm_Socket; MPN SN74HCT125N
U10: MAX232; DIP-16_W7.62mm_Socket; MPN MAX232N

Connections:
+5V: C24.1, C25.1, C28.2, C30.1, JP4.2 (B), R9.1, R11.1, U8.8 (VCC), U9.14 (VCC), U10.10 (T2IN), U10.16 (VCC); also elsewhere on the board
DB9_LB1: J7.1, J7.4, J7.6
DB9_LB2: J7.7, J7.8
DBG_TX: J9.5; also elsewhere on the board
GND: C24.2, C25.2, C29.2, C30.2, J6.2, J7.5, J7.SH (PAD), J8.1, J9.1, R10.2, U8.5 (GND), U9.1, U9.4, U9.7 (GND), U9.10, U9.13, U10.15 (GND); also elsewhere on the board
MAX_C1N: C26.2, U10.3 (C1-)
MAX_C1P: C26.1, U10.1 (C1+)
MAX_C2N: C27.2, U10.5 (C2-)
MAX_C2P: C27.1, U10.4 (C2+)
MAX_VN: C29.1, U10.6 (VS-)
MAX_VP: C28.1, U10.2 (VS+)
MIDI_IN_4: J5.4, R8.1
MIDI_IN_5: D6.2 (A), J5.5, U8.3 (C2)
MIDI_OUT_4: J6.4, R11.2
MIDI_OUT_5: J6.5, R12.2
MIDI_OUT_DRV: R12.1, U9.3
MIDI_RX: JP3.2, JP3.4, JP3.6, TP41.1; also elsewhere on the board
MIDI_RX_OPTO: JP3.1, R9.2, U8.6 (VO2)
MIDI_TX: J8.5, TP40.1, U9.2, U10.11 (T1IN); also elsewhere on the board
OPTO_A: D6.1 (K), R8.2, U8.2 (C1)
OPTO_VB: R10.1, U8.7 (VO1)
PC_RX_RS232: JP3.3, U10.12 (R1OUT)
PWM0: U9.5; also elsewhere on the board
PWM0_EN: U9.6; also elsewhere on the board
PWM1: U9.9; also elsewhere on the board
PWM1_EN: U9.8; also elsewhere on the board
PWM2: U9.12; also elsewhere on the board
PWM2_EN: U9.11; also elsewhere on the board
RS232_RXI: J7.3, U10.13 (R1IN)
RS232_TXO: J7.2, U10.14 (T1OUT)
TTL_RX: J8.4, JP3.5
TTL_VCC: J8.3, JP4.1 (A)
